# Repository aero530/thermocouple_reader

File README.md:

# thermocouple_reader

Handheld 8 channel temperature sensor.  Supports up to 8 type k thermocouples.  Displays temperatures in F or C.

The design uses off the shelf microcontroller board and LCD with a custom thermocouple input board.  The 8 thermocouple channels are muxed to a single interface IC to reduce component costs.  The microcontroller cycles through the mux inputs to read each channel in series, sampling multiple time to mitigate input noise.

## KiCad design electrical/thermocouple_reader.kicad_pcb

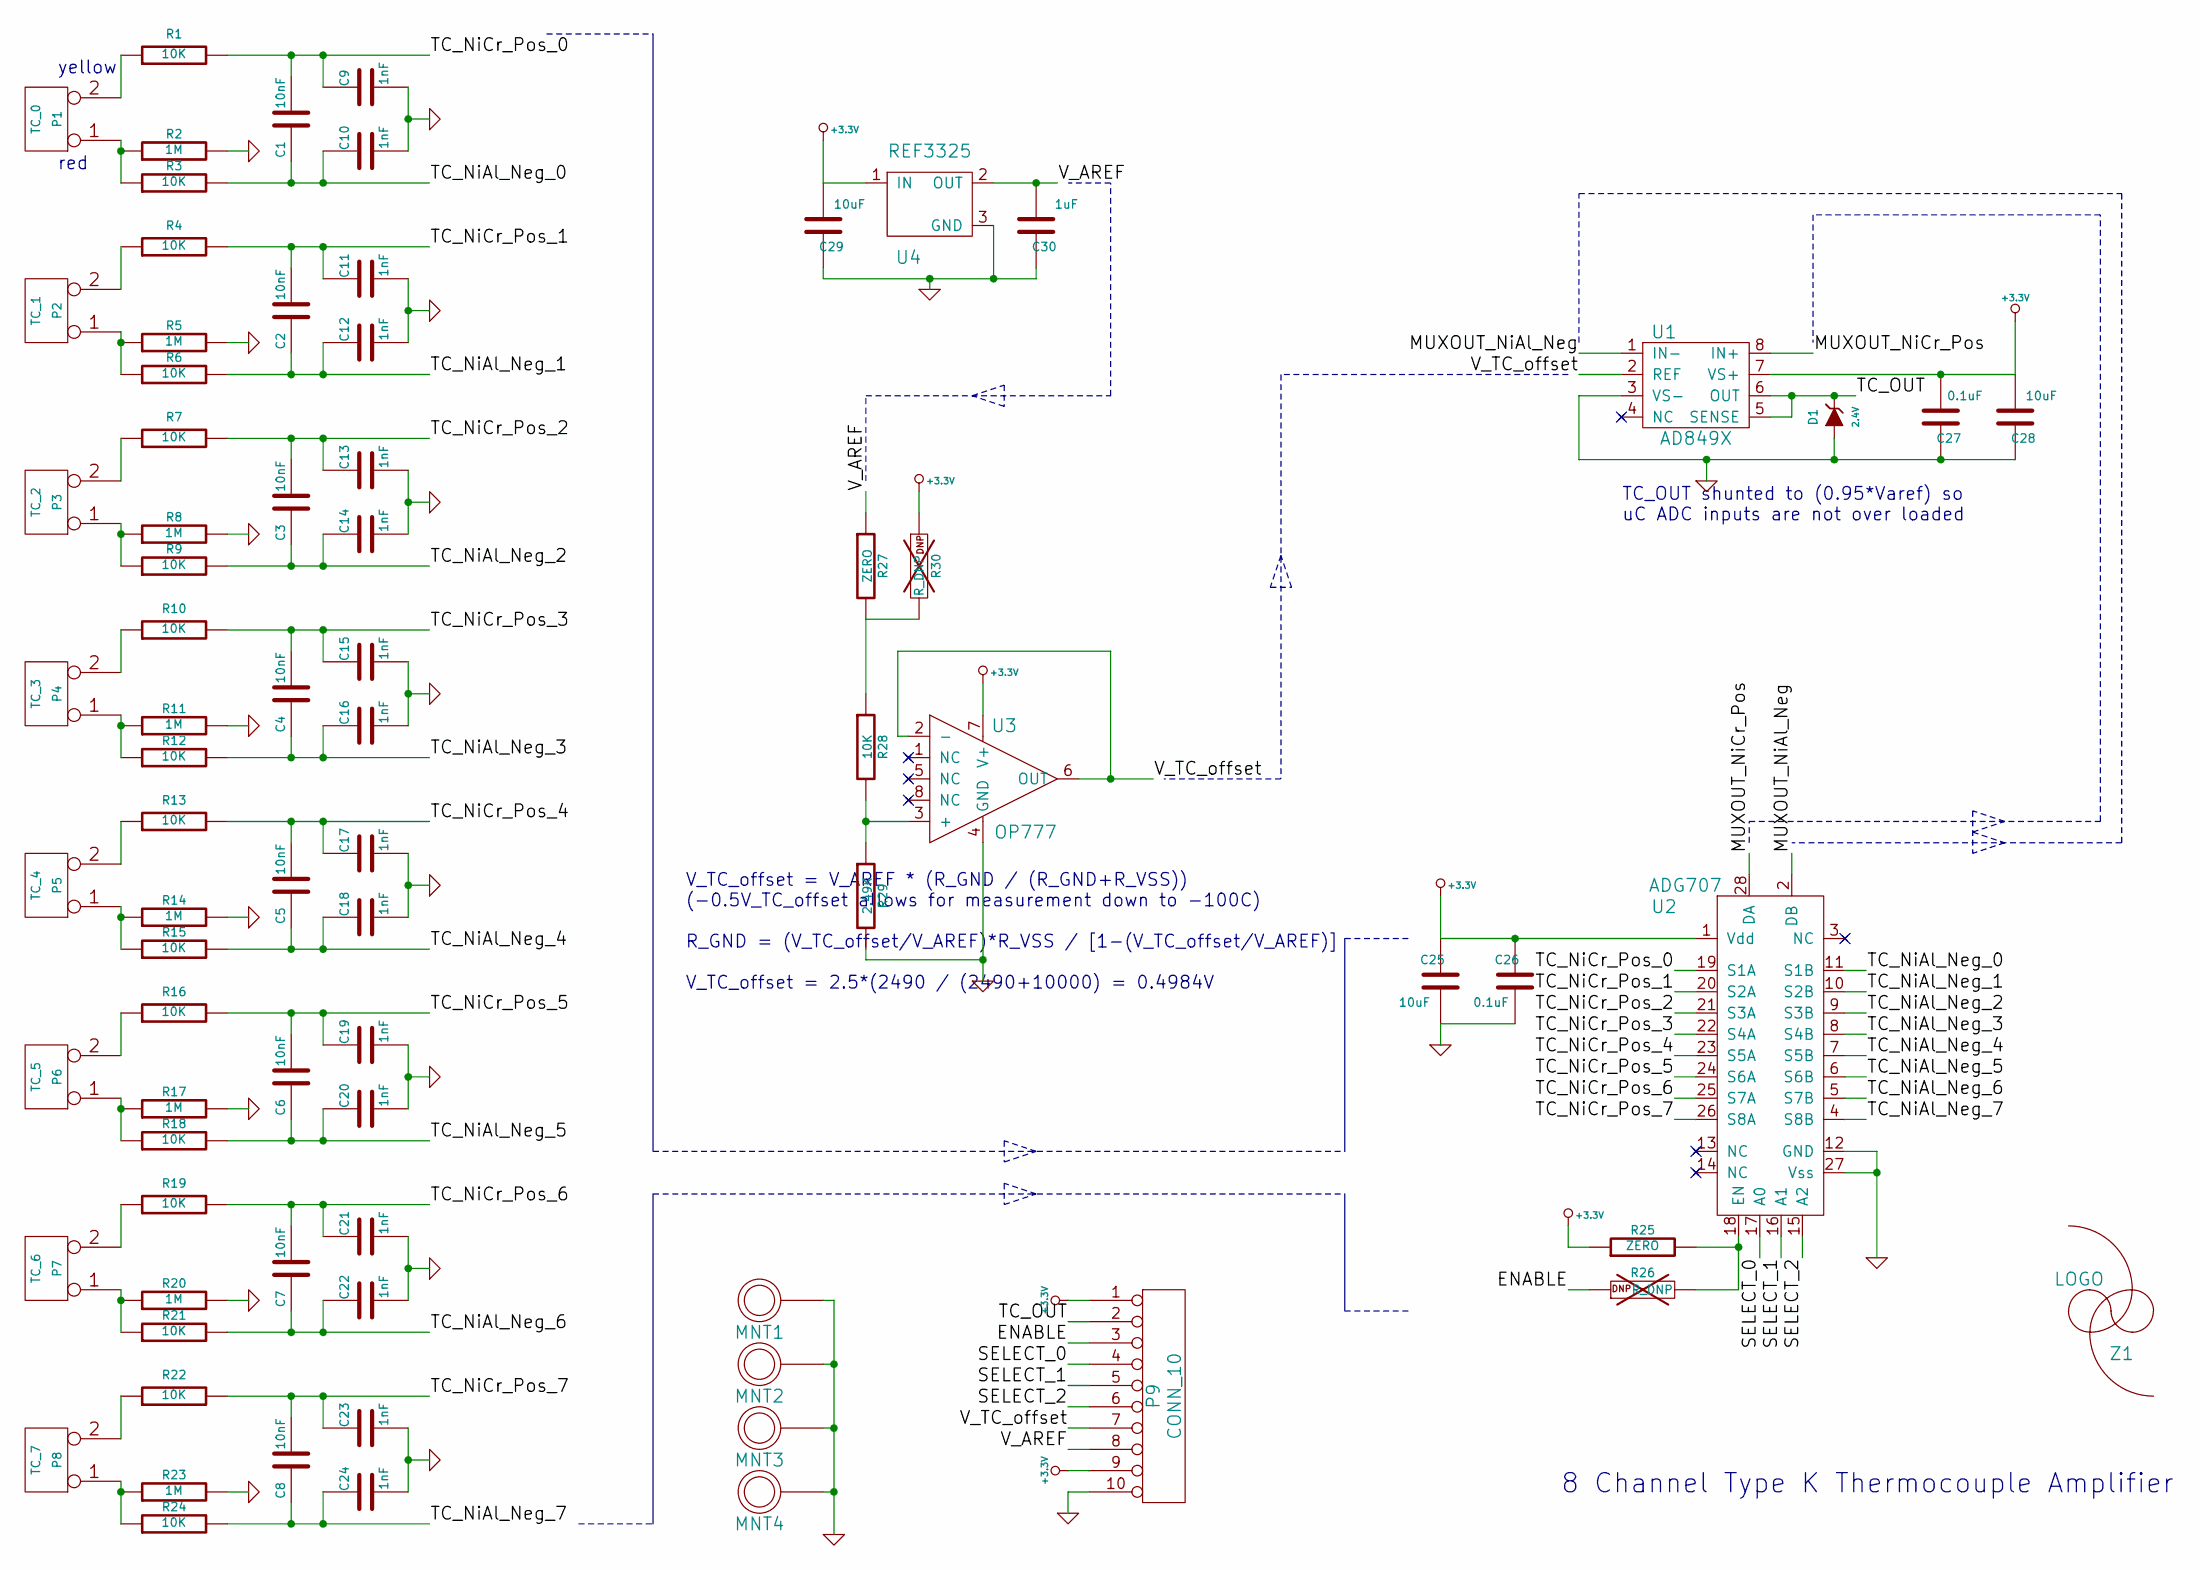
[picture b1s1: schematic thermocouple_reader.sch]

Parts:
C1, C2, C3, C4, C5, C6, C7, C8: 10nF
C9, C10, C11, C12, C13, C14, C15, C16, C17, C18, C19, C20, C21, C22, C23, C24: 1nF
C25, C28, C29: 10uF
C26, C27: 0.1uF
C30: 1uF
D1: 2.4V; Part Number MMBZ5221B-7-F
MNT1, MNT2, MNT3, MNT4: 4_40_HOLE
P1: TC_0
P2: TC_1
P3: TC_2
P4: TC_3
P5: TC_4
P6: TC_5
P7: TC_6
P8: TC_7
P9: CONN_10
R1, R3, R4, R6, R7, R9, R10, R12, R13, R15, R16, R18, R19, R21, R22, R24, R28: 10K
R2, R5, R8, R11, R14, R17, R20, R23: 1M
R25, R27: ZERO
R26, R30: R_DNP
R29: 2.49K
U1: AD849X
U2: ADG707
U3: OP777
U4: REF3325
Z1: LOGO

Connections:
+3.3V: C25.1, C26.1, C27.2, C28.2, C29.2, P9.1, P9.9, R25.1, R30.1, U1.7 (VS+), U2.1 (Vdd), U3.7 (V+), U4.1 (IN)
/ENABLE: P9.3, R26.1
/MUXOUT_NiAl_Neg: U1.1 (IN-), U2.2 (DB)
/MUXOUT_NiCr_Pos: U1.8 (IN+), U2.28 (DA)
/SELECT_0: P9.4, U2.17 (A0)
/SELECT_1: P9.5, U2.16 (A1)
/SELECT_2: P9.6, U2.15 (A2)
/TC_NiAl_Neg_0: C1.1, C10.1, R3.2, U2.11 (S1B)
/TC_NiAl_Neg_1: C2.1, C12.1, R6.2, U2.10 (S2B)
/TC_NiAl_Neg_2: C3.1, C14.1, R9.2, U2.9 (S3B)
/TC_NiAl_Neg_3: C4.1, C16.1, R12.2, U2.8 (S4B)
/TC_NiAl_Neg_4: C5.1, C18.1, R15.2, U2.7 (S5B)
/TC_NiAl_Neg_5: C6.1, C20.1, R18.2, U2.6 (S6B)
/TC_NiAl_Neg_6: C7.1, C22.1, R21.2, U2.5 (S7B)
/TC_NiAl_Neg_7: C8.1, C24.1, R24.2, U2.4 (S8B)
/TC_NiCr_Pos_0: C1.2, C9.1, R1.2, U2.19 (S1A)
/TC_NiCr_Pos_1: C2.2, C11.1, R4.2, U2.20 (S2A)
/TC_NiCr_Pos_2: C3.2, C13.1, R7.2, U2.21 (S3A)
/TC_NiCr_Pos_3: C4.2, C15.1, R10.2, U2.22 (S4A)
/TC_NiCr_Pos_4: C5.2, C17.1, R13.2, U2.23 (S5A)
/TC_NiCr_Pos_5: C6.2, C19.1, R16.2, U2.24 (S6A)
/TC_NiCr_Pos_6: C7.2, C21.1, R19.2, U2.25 (S7A)
/TC_NiCr_Pos_7: C8.2, C23.1, R22.2, U2.26 (S8A)
/TC_OUT: D1.3 (K), P9.2, U1.5 (SENSE), U1.6 (OUT)
/V_AREF: C30.2, P9.8, R27.1, U4.2 (OUT)
/V_TC_offset: P9.7, U1.2 (REF), U3.2 (-), U3.6 (OUT)
GND: C9.2, C10.2, C11.2, C12.2, C13.2, C14.2, C15.2, C16.2, C17.2, C18.2, C19.2, C20.2, C21.2, C22.2, C23.2, C24.2, C25.2, C26.2, C27.1, C28.1, C29.1, C30.1, D1.1 (A), MNT1.1, MNT2.1, MNT3.1, MNT4.1, P9.10, R2.2, R5.2, R8.2, R11.2, R14.2, R17.2, R20.2, R23.2, R29.2, U1.3 (VS-), U2.12 (GND), U2.27 (Vss), U3.4 (GND), U4.3 (GND)
unnamed: P8.2 (PM), R22.1
unnamed: P5.2 (PM), R13.1
unnamed: P4.2 (PM), R10.1
unnamed: P7.2 (PM), R19.1
unnamed: P6.2 (PM), R16.1
unnamed: R25.2, R26.2, U2.18 (EN)
unnamed: R27.2, R28.1, R30.2
unnamed: P3.2 (PM), R7.1
unnamed: P3.1, R8.1, R9.1
unnamed: P2.2 (PM), R4.1
unnamed: P2.1, R5.1, R6.1
unnamed: P4.1, R11.1, R12.1
unnamed: P1.1, R2.1, R3.1
unnamed: P5.1, R14.1, R15.1
unnamed: P1.2 (PM), R1.1
unnamed: R28.2, R29.1, U3.3 (+)
unnamed: P6.1, R17.1, R18.1
unnamed: P8.1, R23.1, R24.1
unnamed: P7.1, R20.1, R21.1

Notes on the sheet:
TC_OUT shunted to (0.95*Varef) so uC ADC inputs are not over loaded
V_TC_offset = V_AREF * (R_GND / (R_GND+R_VSS)) (-0.5V_TC_offset allows for measurement down to -100C) R_GND = (V_TC_offset/V_AREF)*R_VSS / [1-(V_TC_offset/V_AREF)] V_TC_offset = 2.5*(2490 / (2490+10000) = 0.4984V
8 Channel Type K Thermocouple Amplifier
yellow
red

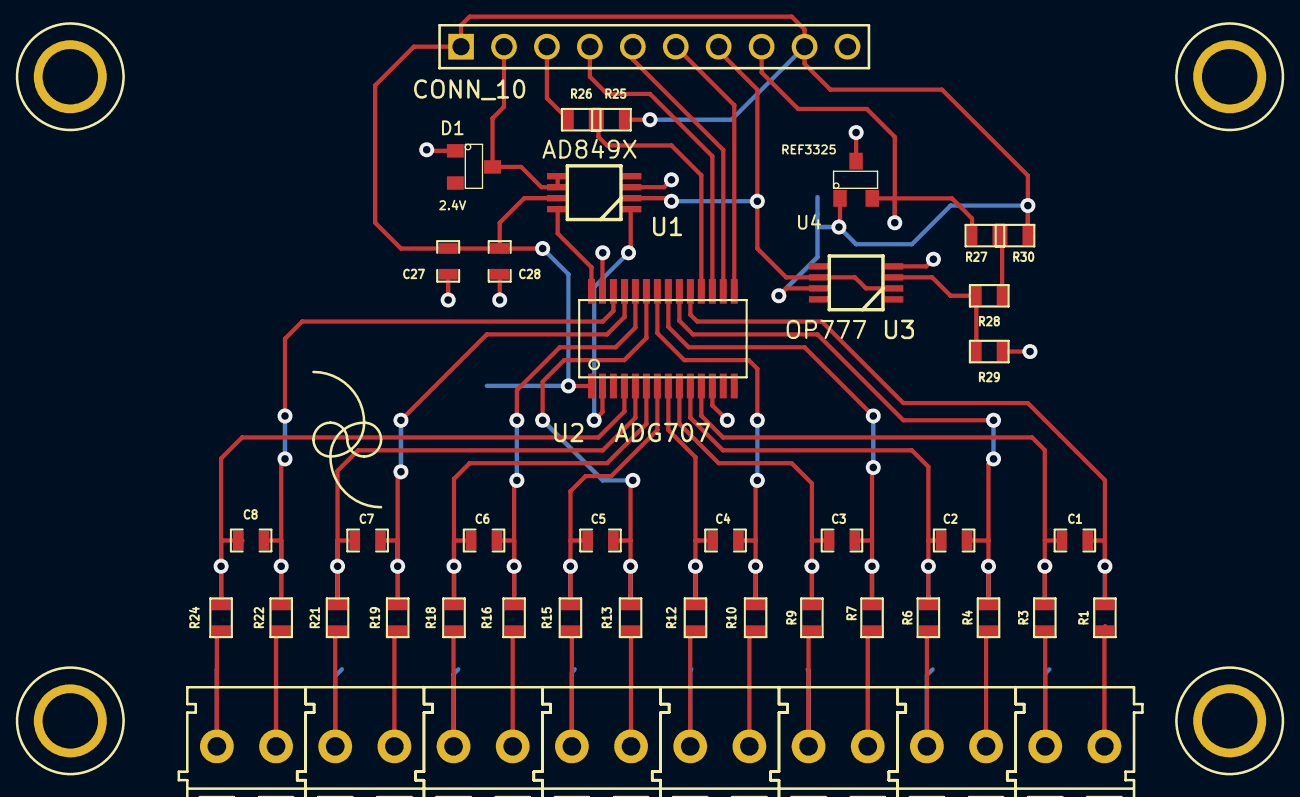
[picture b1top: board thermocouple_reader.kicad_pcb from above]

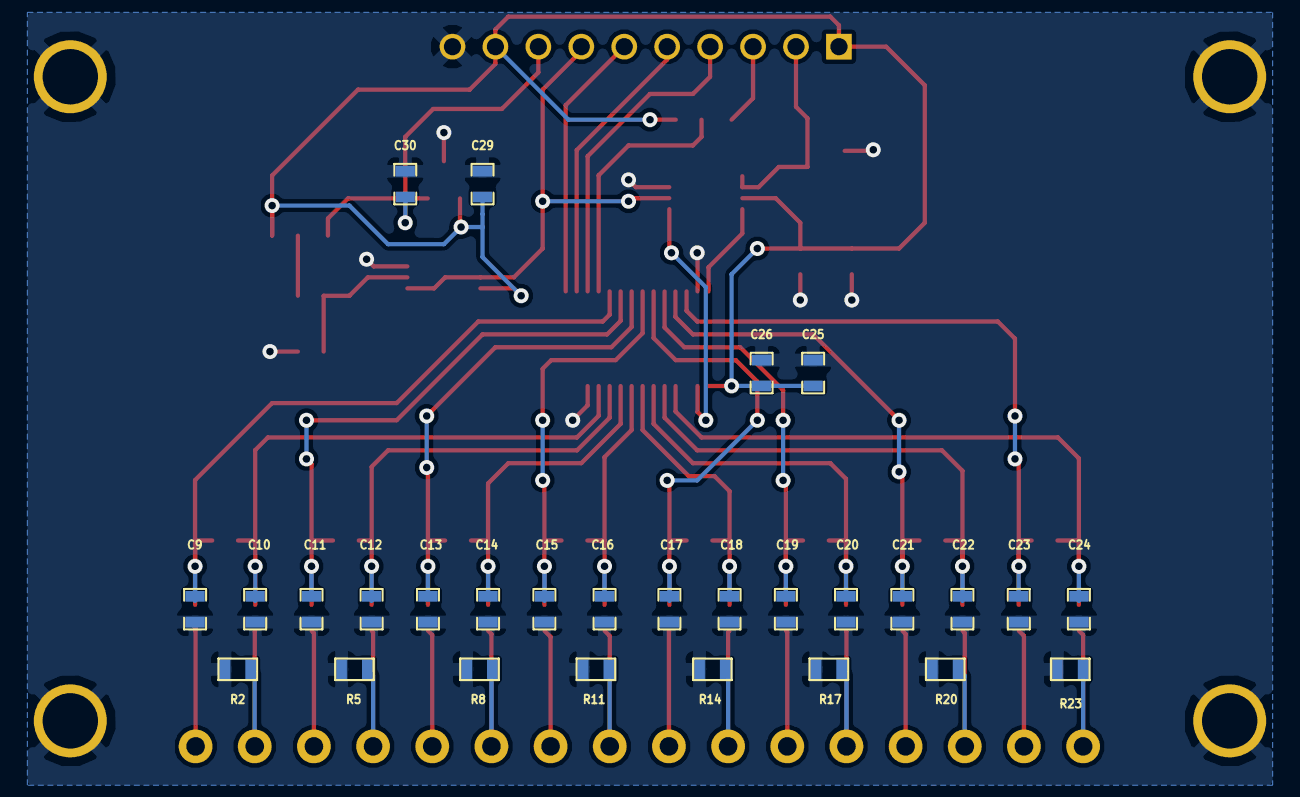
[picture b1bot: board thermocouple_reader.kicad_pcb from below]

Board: 2 copper layers, 79 parts (28 on the bottom side), 46 nets.

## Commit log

2022-02-24 init
2022-03-26 add pic
